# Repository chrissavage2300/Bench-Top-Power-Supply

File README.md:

# Bench-Top-Power-Supply
An Adjustable linear powersupply using the PIC16F1778 with current limiting. Program is done in Great Cow Basic. The schematic was done in Eagle CAD.

Features: 

GLCD:ST7735 but it could easily be a smaller one.

Adjustable Current Limit using encoders.

Adjustable Voltage using encoders.

Clicking the Voltage Adjust knob inward selects either a x1 or x10 multiplier to make adjustment faster. 

Clicking the Current Adjust knob switches between two pre-set voltages, 3.3V and 5V.

The PIC is mostly for displaying voltage and current. The actual control is all done by the op-amp

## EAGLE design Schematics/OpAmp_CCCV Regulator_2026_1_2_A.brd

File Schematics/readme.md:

Note: C6 may not be needed. IC5 and R7 may also not be needed. More testing is required.

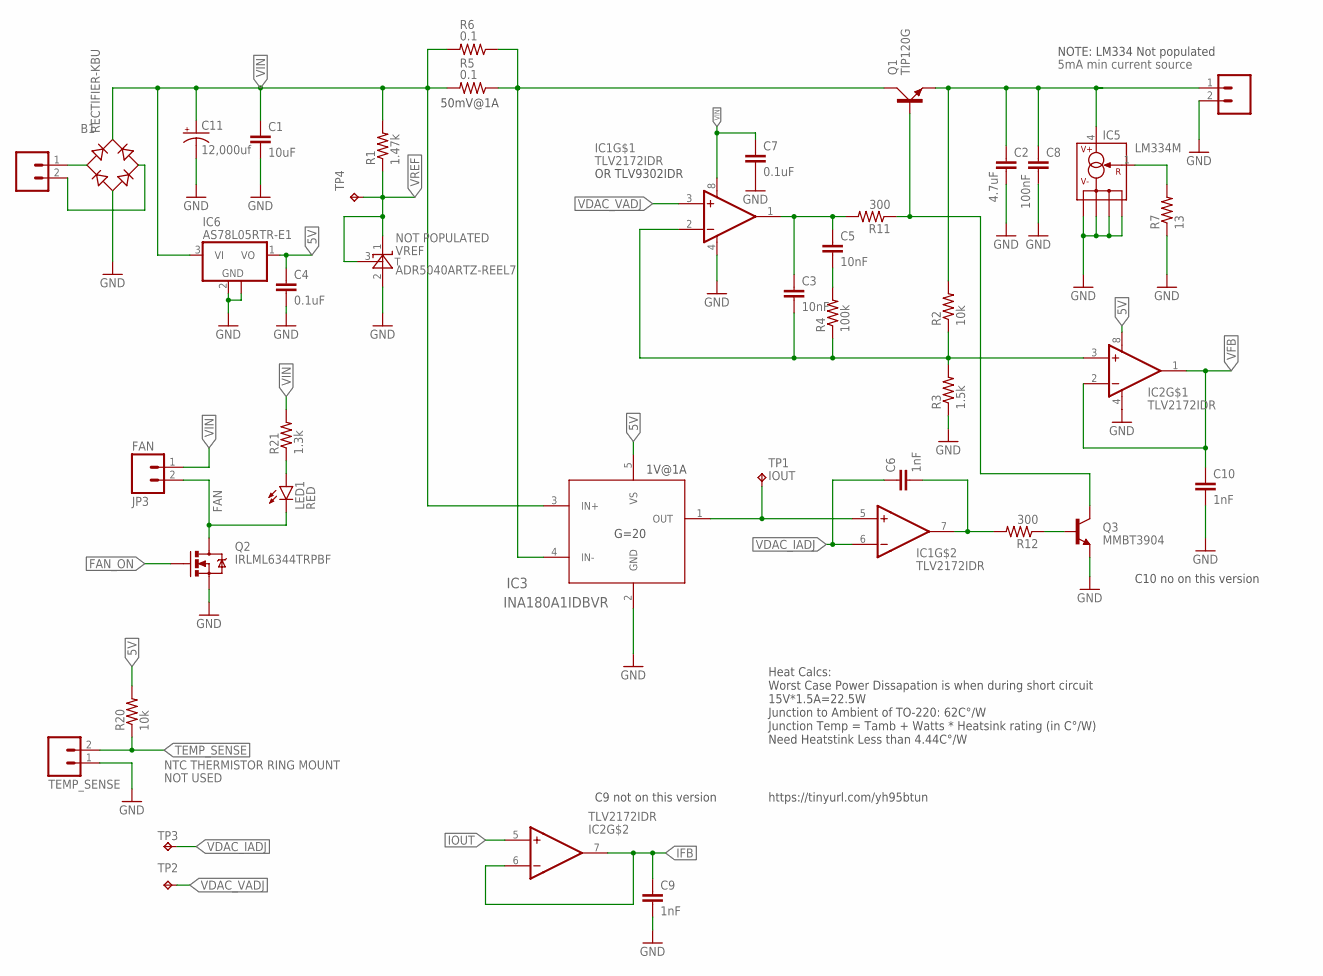
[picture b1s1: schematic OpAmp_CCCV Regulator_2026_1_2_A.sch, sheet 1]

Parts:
B1: RECTIFIER-KBU; KBU
C1: 10uF; 1206
C2: 4.7uF; 1206
C3, C5: 10nF; 0805
C4: 0.1uF; 1206
C6, C9, C10: 1nF; 0805
C7: 0.1uF; 0805
C8: 100nF; 1206
C11: 12,000uf; EB25D
IC1, IC2: TLV2172IDR; SOIC8
IC3: INA180A1IDBVR; DBV0005A_N
IC5: LM334M; SO08
IC6: AS78L05RTR-E1; SOT89
JP1: M023.5MM_LOCK; SCREWTERMINAL-3.5MM-2_LOCK
JP2: M023.5MM; SCREWTERMINAL-3.5MM-2
JP3: FAN; MOLEX-1X2_LOCK
JP4: TEMP_SENSE; 1X02
LED1: RED; LED-1206
Q1: TIP120G; TO220AV
Q2: IRLML6344TRPBF; SOT323
Q3: MMBT3904; SOT23
R1: 1.47k; 1206
R2, R20: 10k; 1206
R3: 1.5k; 1206
R4: 100k; 0805
R5, R6: 0.1; 1206
R7: 13; 1206
R11, R12: 300; 0805
R21: 1.3k; 1206
TP1, TP2, TP3, TP4: TPTP20R; TP20R
VREF: ADR5040ARTZ-REEL7; RT_3_ADI

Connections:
5V: C4.1, IC2.8 (V+), IC3.5 (VS), IC6.1 (VO), R20.2; also elsewhere on the board
AC: B1.AC1, JP1.1
COMP: C3.1, C5.1, IC1.1 (OUT), R11.2
FAN: JP3.2, LED1.C, Q2.3 (D)
FAN_ON: Q2.1 (G); also elsewhere on the board
FB: C3.2, IC1.2 (-IN), IC2.3 (+IN), R2.1, R3.2, R4.1
GND: B1.-, C1.2, C2.2, C4.2, C7.2, C8.2, C9.2, C10.2, C11.-, IC1.4 (V-), IC2.4 (V-), IC3.2 (GND), IC5.2 (V-), IC5.3 (V-), IC5.6 (V-), IC5.7 (V-), IC6.2 (GND), IC6.2@1 (GND), JP2.2, JP4.1, Q2.2 (S), Q3.2 (E), R3.1, R7.1, VREF.2 (A); also elsewhere on the board
IFB: C9.1, IC2.6 (-IN), IC2.7 (OUT); also elsewhere on the board
IOUT: IC1.5 (+IN), IC2.5 (+IN), IC3.1 (OUT), TP1.TP
IOUTA: C6.2, IC1.7 (OUT), R12.2
unnamed: C5.2, R4.2
unnamed: B1.AC2, JP1.2
unnamed: IC5.1 (R), R7.2
unnamed: Q3.1 (B), R12.1
unnamed: LED1.A, R21.1
PASS_BASE: Q1.B, Q3.3 (C), R11.1
TEMP_SENSE: JP4.2, R20.1; also elsewhere on the board
VDAC_IADJ: C6.1, IC1.6 (-IN), TP3.TP; also elsewhere on the board
VDAC_VADJ: IC1.3 (+IN), TP2.TP; also elsewhere on the board
VFB: C10.1, IC2.1 (OUT), IC2.2 (-IN); also elsewhere on the board
VIN: B1.+, C1.1, C7.1, C11.+, IC1.8 (V+), IC3.3 (IN+), IC6.3 (VI), JP3.1, R1.2, R5.2, R6.2, R21.2
VIN2: IC3.4 (IN-), Q1.C, R5.1, R6.1
VOUT: C2.1, C8.1, IC5.4 (V+), JP2.1, Q1.E, R2.2
VREF: R1.1, TP4.TP, VREF.1 (C), VREF.3 (T); also elsewhere on the board

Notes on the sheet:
G=20
50mV@1A
1V@1A
https://tinyurl.com/yh95btun
5mA min current source
Heat Calcs: Worst Case Power Dissapation is when during short circuit 15V*1.5A=22.5W Junction to Ambient of TO-220: 62C°/W Junction Temp = Tamb + Watts * Heatsink rating (in C°/W) Need Heatstink Less than 4.44C°/W
NTC THERMISTOR RING MOUNT
OR TLV9302IDR
NOTE: LM334 Not populated
C9 not on this version
C10 no on this version
NOT POPULATED
NOT USED

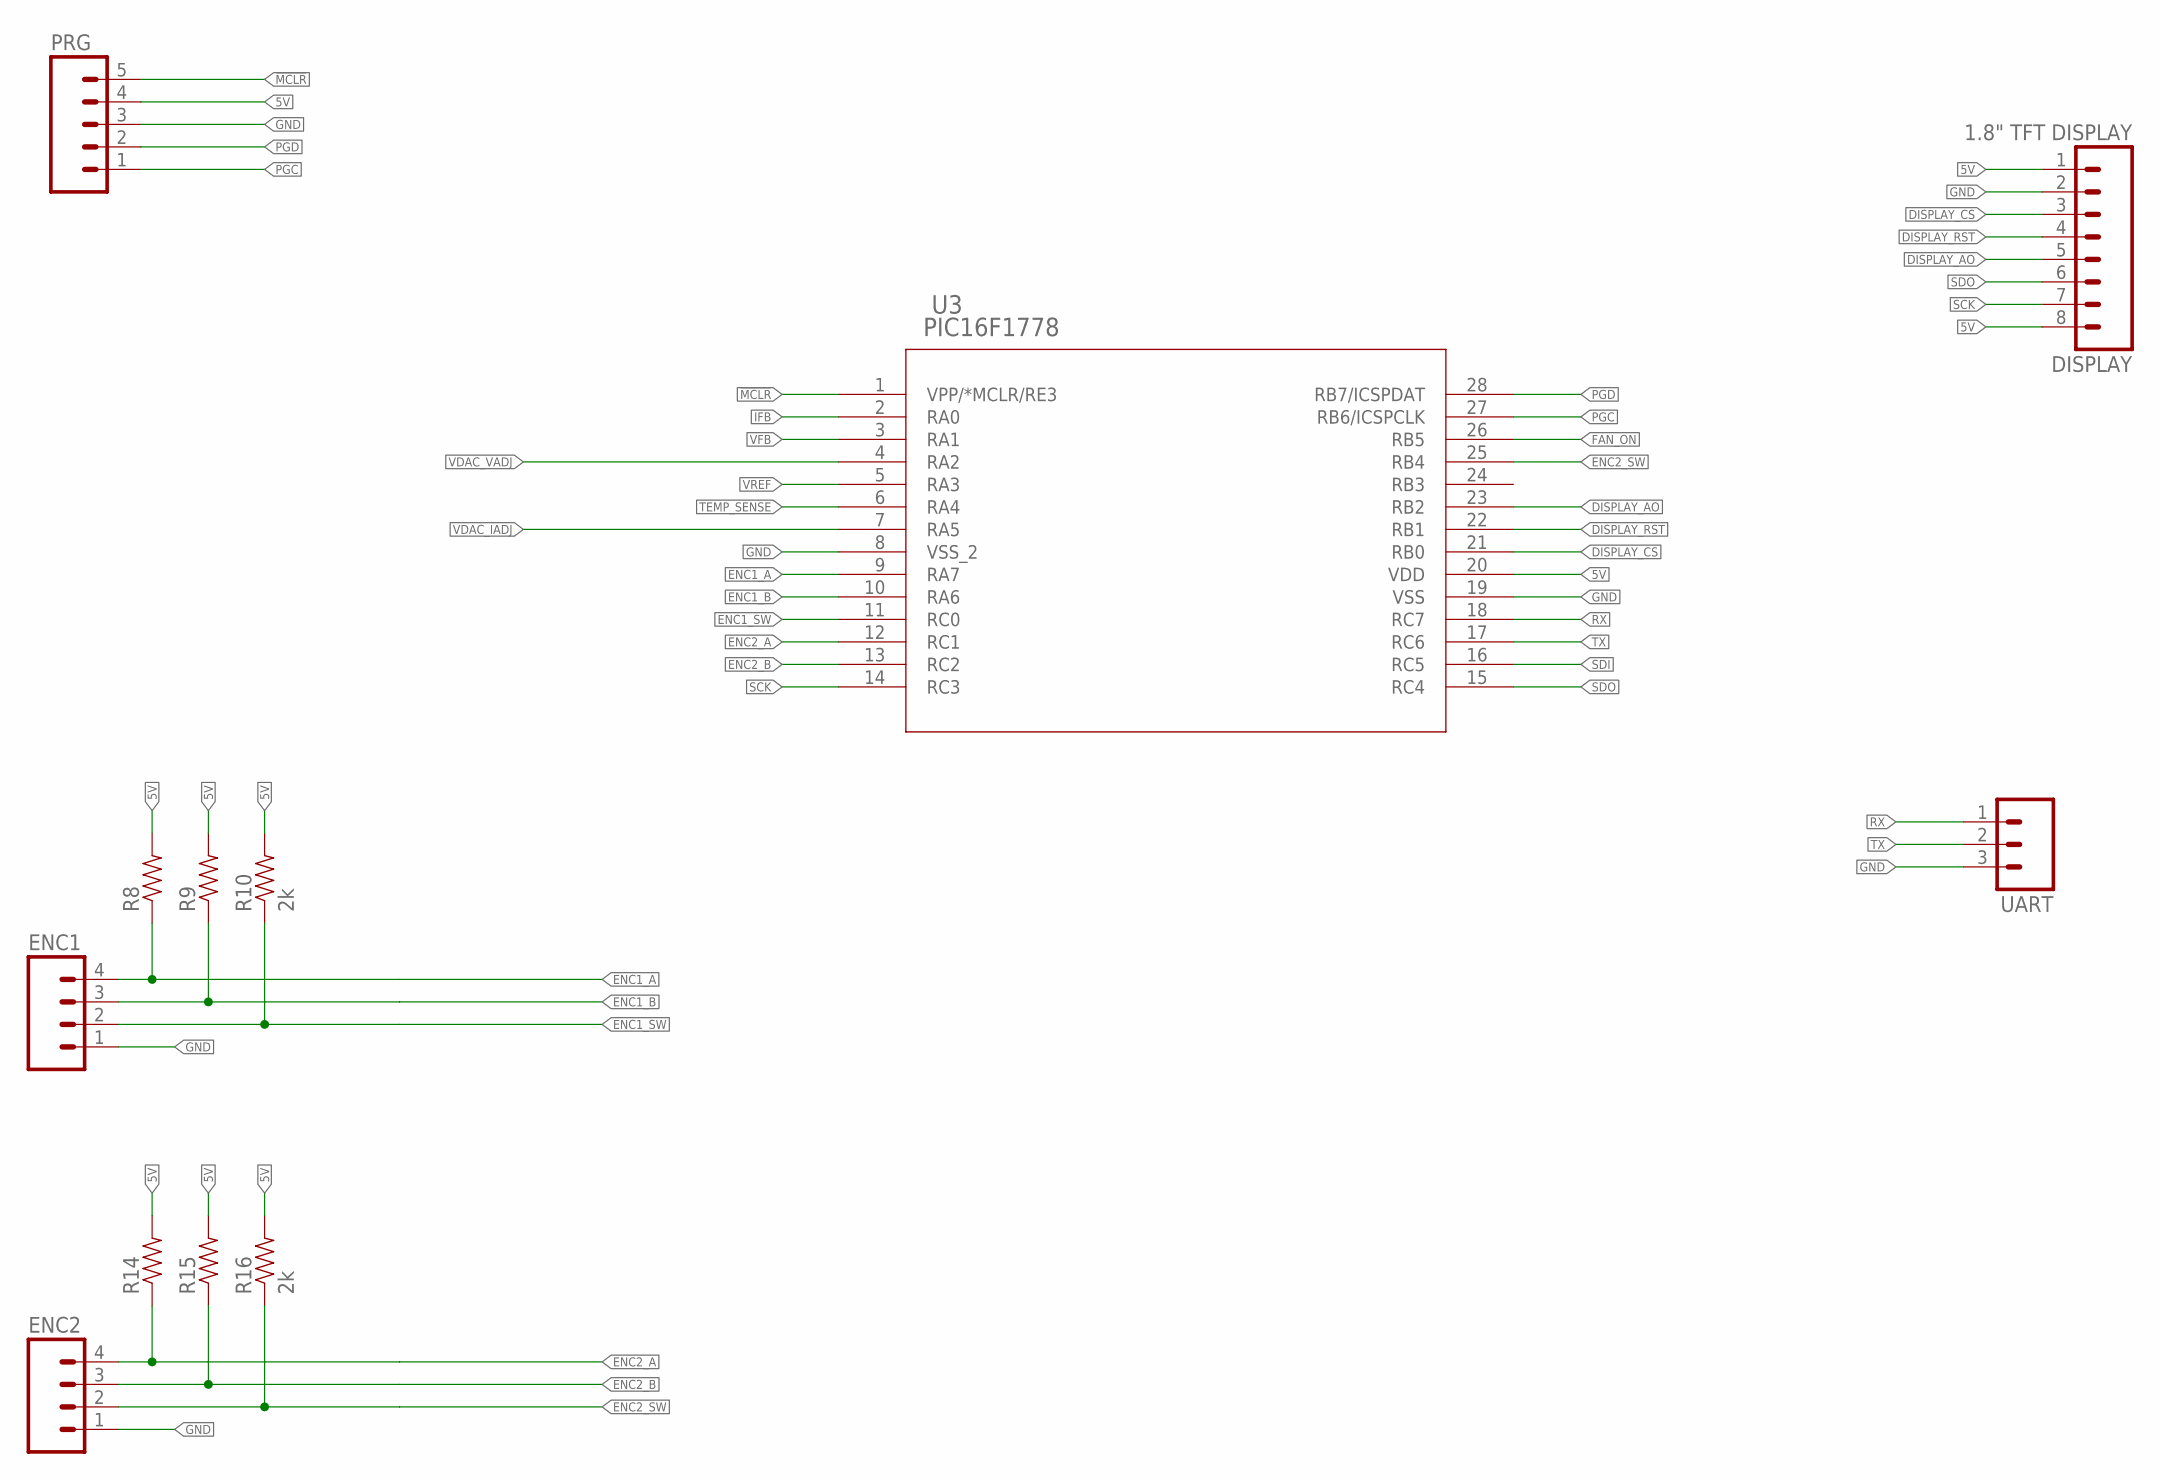
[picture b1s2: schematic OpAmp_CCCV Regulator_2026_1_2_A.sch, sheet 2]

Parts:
DISPLAY: 1.8" TFT DISPLAY; 1X08_LOCK_LONGPADS
ENC1, ENC2: M04LOCK_LONGPADS; 1X04_LOCK_LONGPADS
PRG: M05LOCK; 1X05_LOCK
R8, R9, R10, R14, R15, R16: 2k; 0805
U3: PIC16F1778; SOIC28-W_MC
UART: M03LOCK_LONGPADS; 1X03_LOCK_LONGPADS

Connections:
5V: DISPLAY.1, DISPLAY.8, PRG.4, R8.2, R9.2, R10.2, R14.2, R15.2, R16.2, U3.20 (VDD); also elsewhere on the board
!MCLR: PRG.5, U3.1 (VPP/*MCLR/RE3)
DISPLAY_AO: DISPLAY.5, U3.23 (RB2)
DISPLAY_CS: DISPLAY.3, U3.21 (RB0)
DISPLAY_RST: DISPLAY.4, U3.22 (RB1)
ENC1_A: ENC1.4, R8.1, U3.9 (RA7)
ENC1_B: ENC1.3, R9.1, U3.10 (RA6)
ENC1_SW: ENC1.2, R10.1, U3.11 (RC0)
ENC2_A: ENC2.4, R14.1, U3.12 (RC1)
ENC2_B: ENC2.3, R15.1, U3.13 (RC2)
ENC2_SW: ENC2.2, R16.1, U3.25 (RB4)
FAN_ON: U3.26 (RB5); also elsewhere on the board
GND: DISPLAY.2, ENC1.1, ENC2.1, PRG.3, U3.8 (VSS_2), U3.19 (VSS), UART.3; also elsewhere on the board
IFB: U3.2 (RA0); also elsewhere on the board
PGC: PRG.1, U3.27 (RB6/ICSPCLK)
PGD: PRG.2, U3.28 (RB7/ICSPDAT)
RX: U3.18 (RC7), UART.1
SCK: DISPLAY.7, U3.14 (RC3)
SDI: U3.16 (RC5)
SDO: DISPLAY.6, U3.15 (RC4)
TEMP_SENSE: U3.6 (RA4); also elsewhere on the board
TX: U3.17 (RC6), UART.2
VDAC_IADJ: U3.7 (RA5); also elsewhere on the board
VDAC_VADJ: U3.4 (RA2); also elsewhere on the board
VFB: U3.3 (RA1); also elsewhere on the board
VREF: U3.5 (RA3); also elsewhere on the board

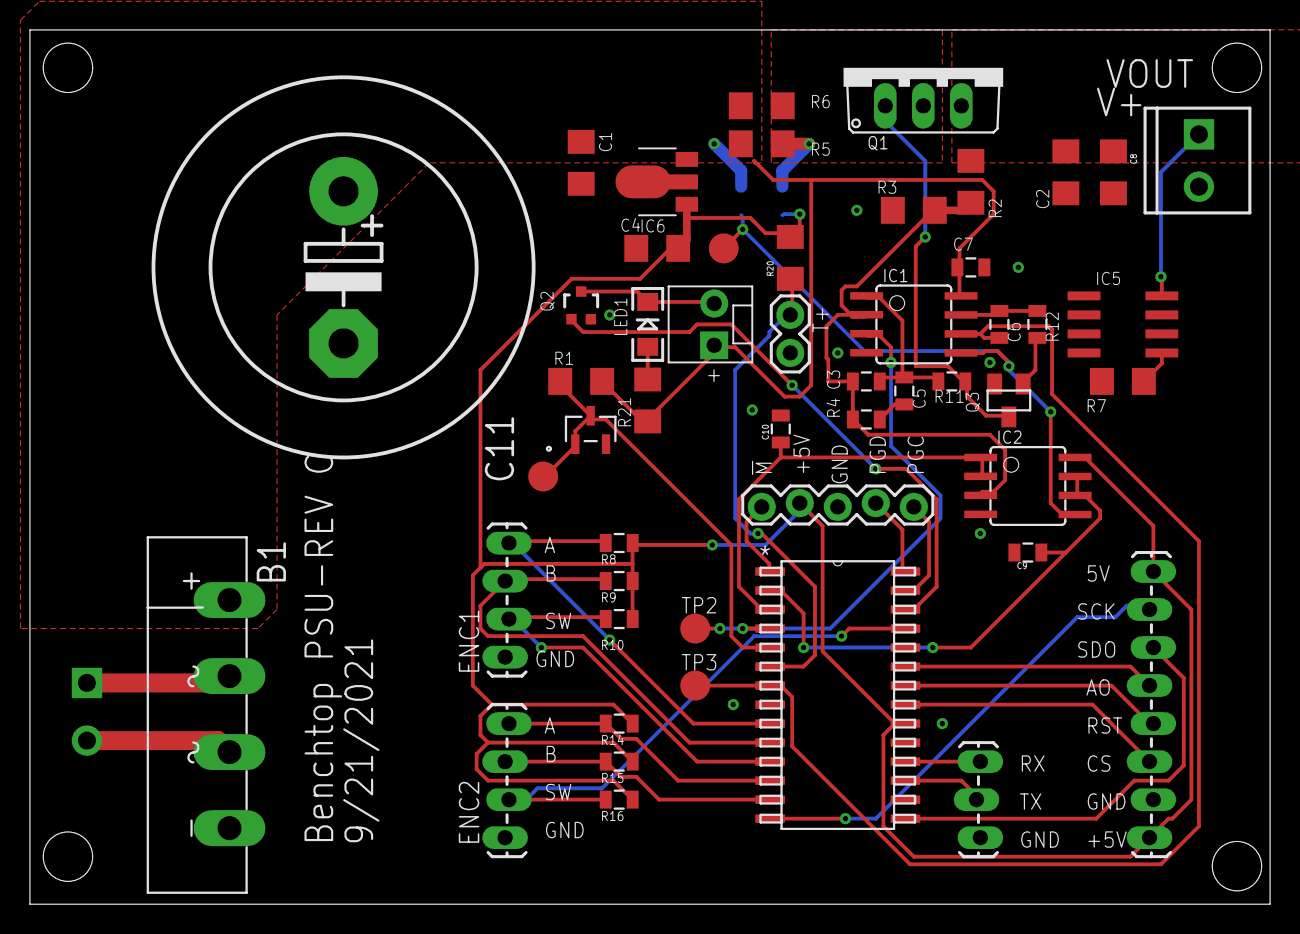
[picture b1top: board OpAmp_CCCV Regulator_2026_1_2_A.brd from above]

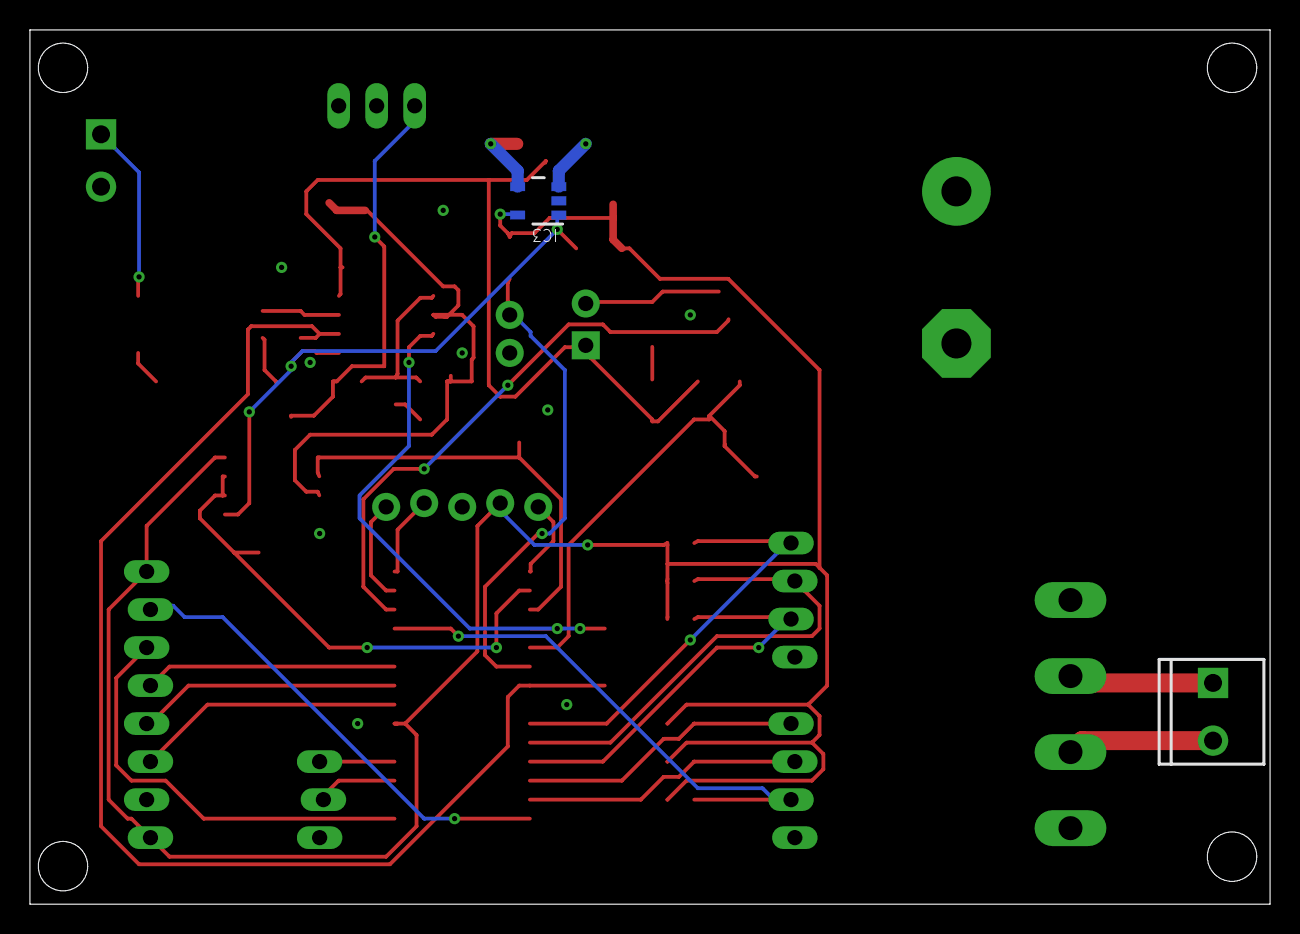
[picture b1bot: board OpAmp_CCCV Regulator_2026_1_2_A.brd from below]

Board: 2 copper layers, 82.9 x 58.4 mm, 53 parts (2 on the bottom side), 40 nets.

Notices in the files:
parts and their libraries:
SparkFun-Resistors: Licensing: Creative Commons ShareAlike 4.0 International - https://creativecommons.org/licenses/by-sa/4.0
SparkFun: Licensing: CC v3.0 Share-Alike You are welcome to use this library for commercial purposes.
COPYRIGHT: Copyright (C) 2016 Accelerated Designs. All rights reserved
